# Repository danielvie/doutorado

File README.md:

# Doutorado

Repository for thesis writing, simulations, embedded experiments, presentations, publications, and supporting research material.

## Quick links

- Current thesis PDF: [`tese.pdf`](tese.pdf)
- Repository map: [`docs/REPO_MAP.md`](docs/REPO_MAP.md)
- Domain glossary: [`CONTEXT.md`](CONTEXT.md)
- Archived old root README notes: [`docs/README_NOTES_ARCHIVE.md`](docs/README_NOTES_ARCHIVE.md)
- Current working TODO/history: [`TODO`](TODO)

## Where to go

| Need | Go to |
| --- | --- |
| Thesis and paper LaTeX sources | [`LATEX/`](LATEX/) |
| Plans, TODOs, and qualification material | [`research-material/planning/`](research-material/planning/) |
| Reviewer comments | [`research-material/review-feedback/`](research-material/review-feedback/) |
| Authored analysis and meeting notes | [`research-material/working-notes/`](research-material/working-notes/) |
| Shared diagrams and writing assets | [`assets/`](assets/) |
| Current MATLAB simulations/control code | [`simulations/matlab-sim/`](simulations/matlab-sim/) |
| Older MATLAB simulations | [`simulations/legacy/`](simulations/legacy/) |
| Projection/feasibility-region MATLAB work | [`simulations/projection/`](simulations/projection/) |
| ESP32 firmware, hardware docs, and web UI | [`embedded/`](embedded/) |
| External papers, books, theses, and course material | [`research-material/literature/`](research-material/literature/) |
| Presentations and slides | [`presentations/`](presentations/) |
| External/vendor material | [`z_dependencies/`](z_dependencies/), [`z_kawa/`](z_kawa/), [`z_mpt_install/`](z_mpt_install/), and [`z_qpoases/`](z_qpoases/) |

## Common commands

This repository uses [`Taskfile.yml`](Taskfile.yml):

```sh
task --list
```

Important tasks:

- `task run` opens generated overview documentation.
- `task test` validates generated overview documentation.
- `task clean` removes generated overview documentation.
- `task update-tese` copies `LATEX/thesis/build/tese.pdf` to the repository root.

## Navigation conventions

- Start from this README, then use [`docs/REPO_MAP.md`](docs/REPO_MAP.md) for locations and [`CONTEXT.md`](CONTEXT.md) for terminology.
- Prefer area-specific READMEs/docs when they exist.
- Treat `z_dependencies/`, `z_kawa/`, `z_mpt_install/`, `z_qpoases/`, and `simulations/backup/` as backup, vendored, or auxiliary material unless a task explicitly points there.
- Prefer `simulations/matlab-sim/` over `simulations/legacy/` for current simulation work.
- Prefer `embedded/esp32_idf/` for current ESP32 firmware work.
- Avoid adding new loose files at the repository root; put new material in the closest project area.
- Keep document navigation folders at most three levels deep. Self-contained source/build trees are exempt when flattening would break them.

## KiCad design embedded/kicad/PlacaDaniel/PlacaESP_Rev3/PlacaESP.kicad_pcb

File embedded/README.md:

# Projeto embarcado

Workspace do projeto de doutorado para controle em tempo real com ESP32.

## Estrutura

- [`esp32_idf/`](esp32_idf/) — firmware ESP-IDF, protocolo BLE, interface web e documentação técnica do controlador de sinais.
- [`kicad/`](kicad/) — fontes das placas, bibliotecas de footprints/símbolos e arquivos de fabricação.
- [`docs-hardware/`](docs-hardware/) — pinagens, diagramas de conexão e datasheets de referência.
- [`tests_espressif/`](tests_espressif/) — experimentos independentes com ESP32/PlatformIO.

## Firmware

Consulte [`esp32_idf/README.md`](esp32_idf/README.md) para a arquitetura e os requisitos do firmware. Para listar os comandos disponíveis:

```sh
cd esp32_idf
task --list
```

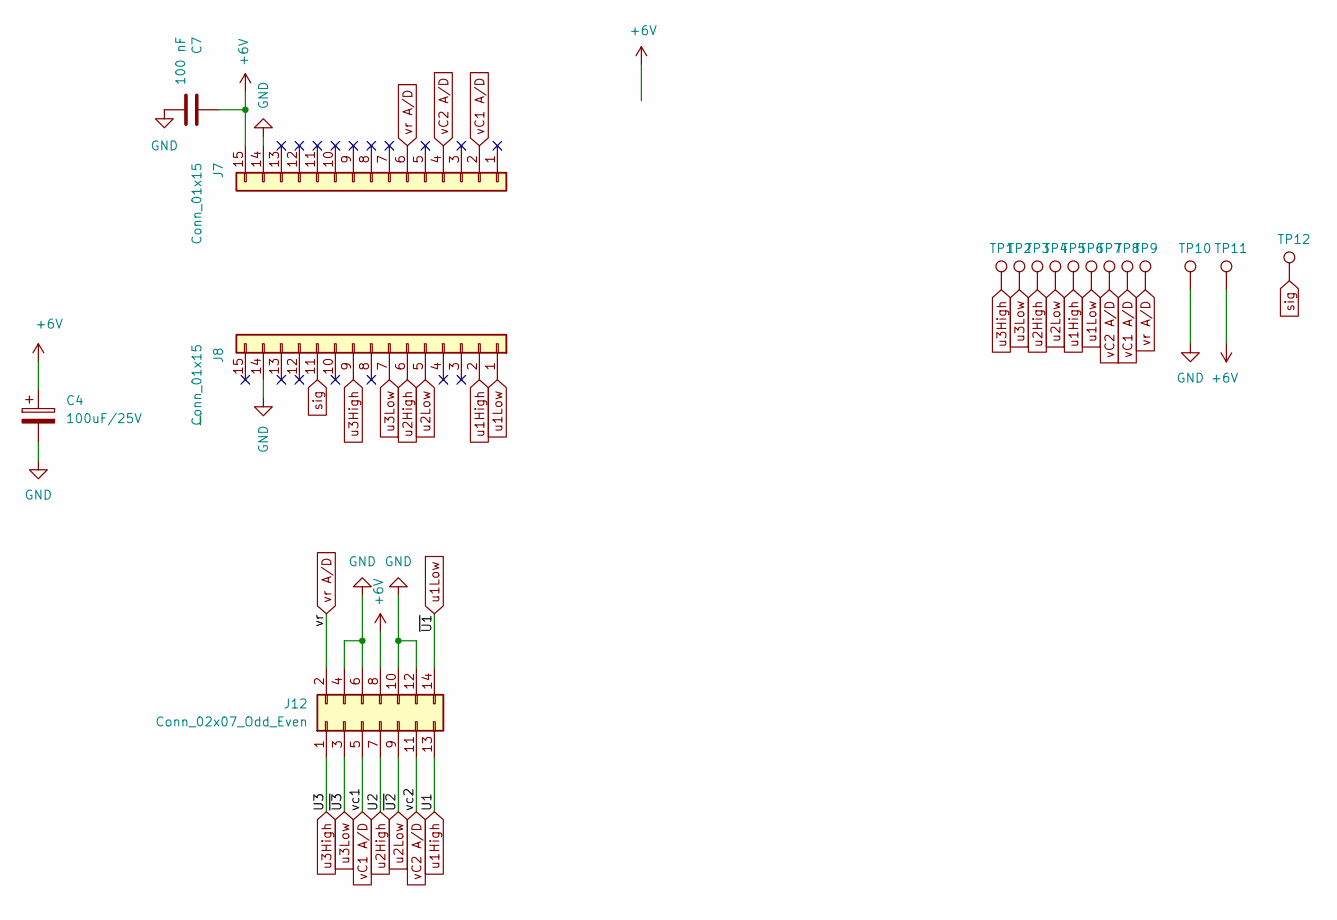
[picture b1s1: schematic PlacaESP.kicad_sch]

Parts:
C4: 100uF/25V; CP_Radial_D6.3mm_P2.50mm
C7: 100 nF; C_Disc_D6.0mm_W2.5mm_P5.00mm
J7, J8: Conn_01x15; PinSocket_1x15_P2.54mm_Vertical
J12: Conn_02x07_Odd_Even; IDC-Header_2x07_P2.54mm_Vertical
TP1, TP2, TP3, TP4, TP5, TP6, TP7, TP8, TP9, TP10, TP11, TP12: TestPoint_Bridge_Pitch2.54mm_Drill0.7mm

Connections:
+6V: C4.1, C7.1, J7.15, J12.8, TP11.1
GND: C4.2, C7.2, J7.14, J8.14, J12.4, J12.6, J12.10, J12.12, TP10.1
sig: J8.11, TP12.1
u1High: J8.2, J12.13, TP5.1
u1Low: J8.1, J12.14, TP6.1
u2High: J8.6, J12.7, TP3.1
u2Low: J8.5, J12.9, TP4.1
u3High: J8.9, J12.1, TP1.1
u3Low: J8.7, J12.3, TP2.1
vC1 A/D: J7.2, J12.5, TP8.1
vC2 A/D: J7.4, J12.11, TP7.1
vr A/D: J7.6, J12.2, TP9.1

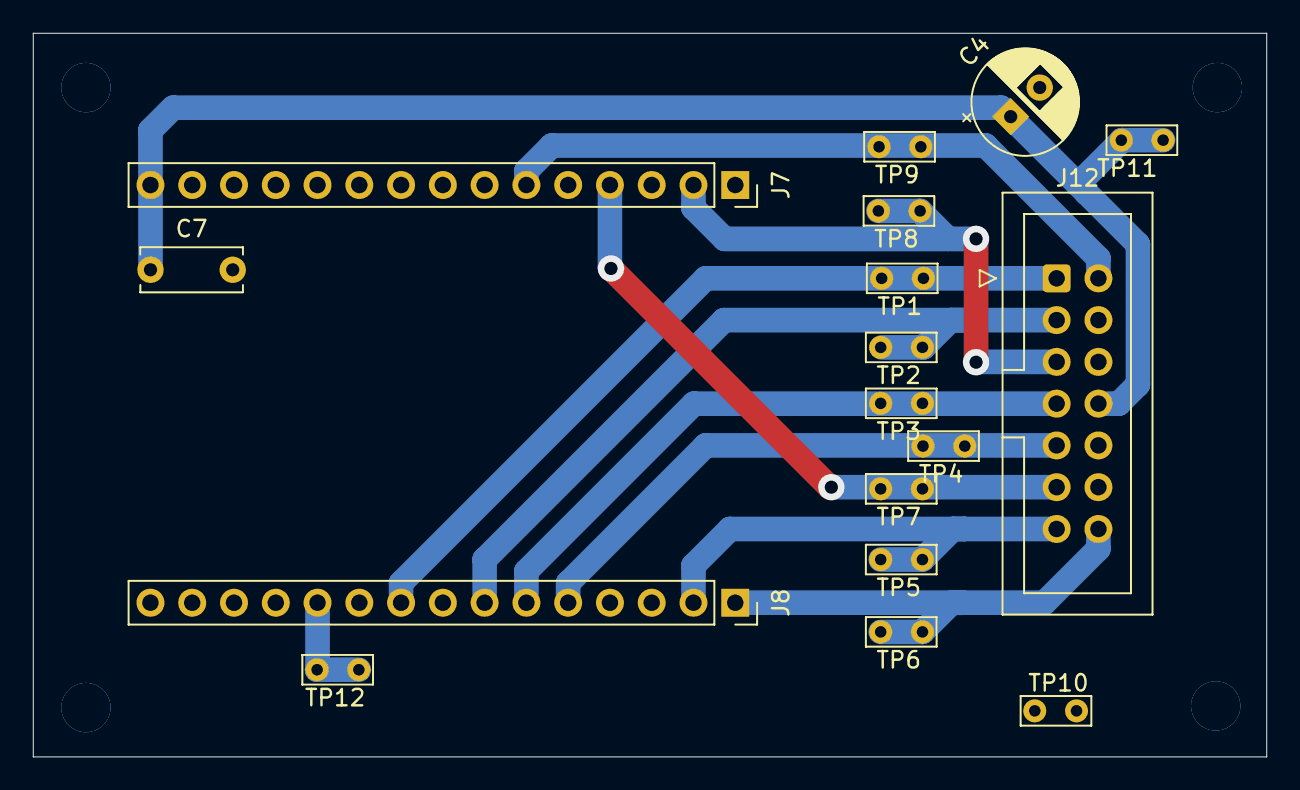
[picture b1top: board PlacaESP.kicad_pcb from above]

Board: 2 copper layers, 75.0 x 44.0 mm, 17 parts (0 on the bottom side), 12 nets.

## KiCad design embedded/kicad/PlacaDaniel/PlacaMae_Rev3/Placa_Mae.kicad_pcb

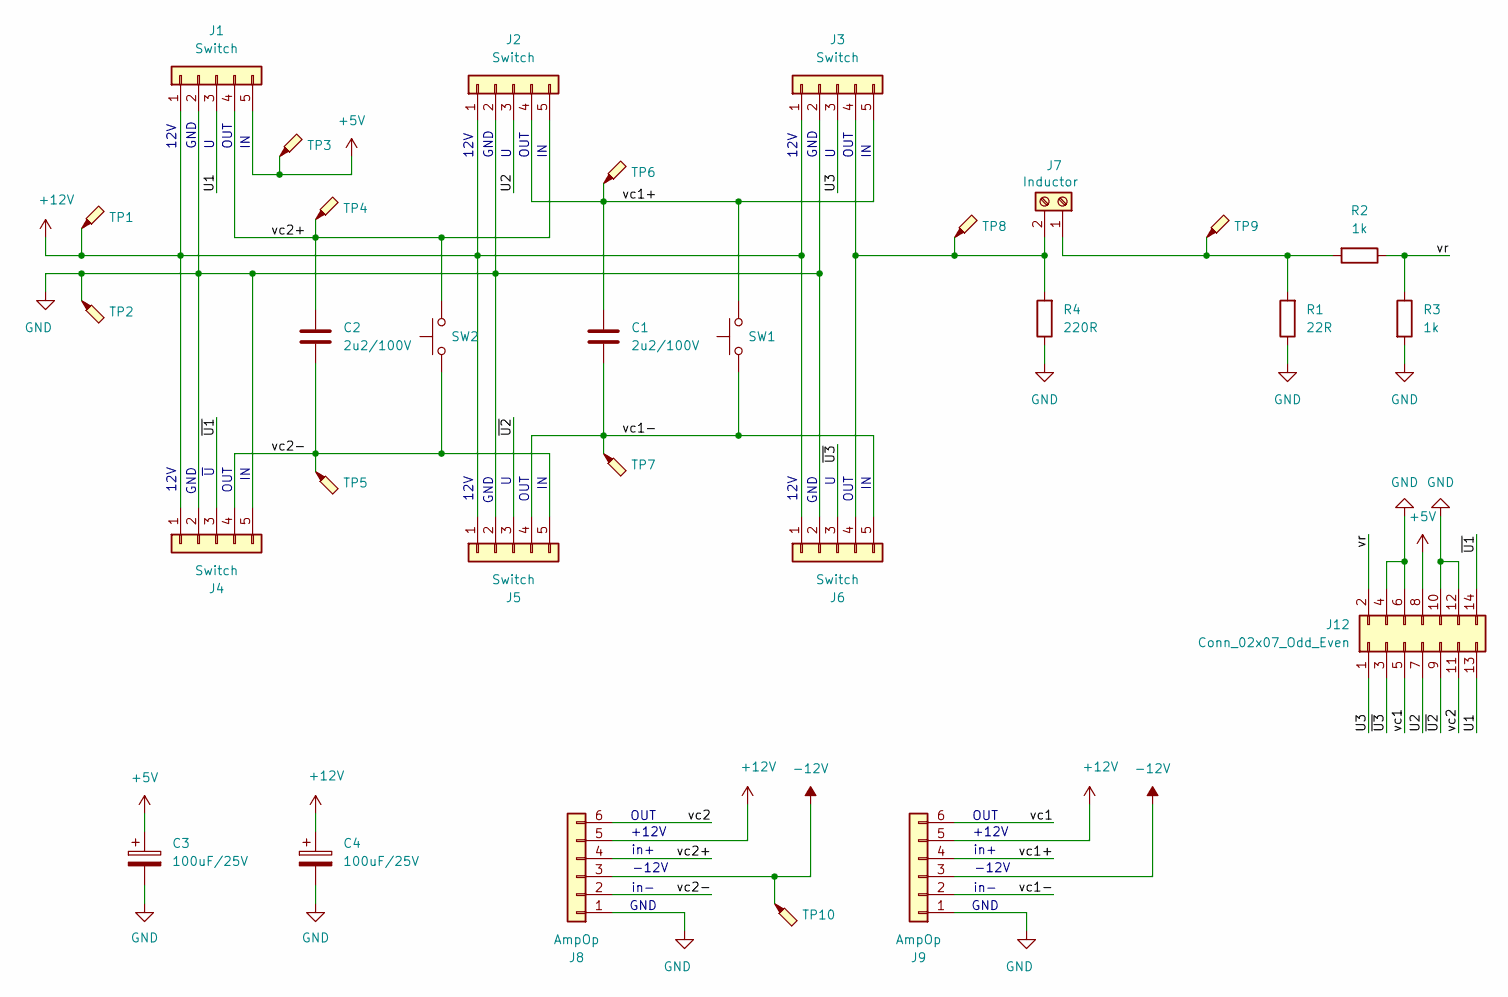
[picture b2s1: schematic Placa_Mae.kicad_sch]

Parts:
C1, C2: 2u2/100V; C_Rect_L29.0mm_W9.1mm_P27.50mm_MKT
C3, C4: 100uF/25V; CP_Radial_D6.3mm_P2.50mm
J1, J2, J3, J4, J5, J6: Switch; TerminalBlock_Xinya_XY308-2.54-5P_1x05_P2.54mm_Horizontal
J7: Inductor; TerminalBlock_Phoenix_MKDS-1,5-2_1x02_P5.00mm_Horizontal
J8, J9: AmpOp; TerminalBlock_Xinya_XY308-2.54-6P_1x06_P2.54mm_Horizontal
J12: Conn_02x07_Odd_Even; IDC-Header_2x07_P2.54mm_Vertical
R1: 22R; R_Axial_DIN0516_L15.5mm_D5.0mm_P25.40mm_Horizontal
R2, R3: 1k; R_1206_3216Metric_Pad1.30x1.75mm_HandSolder
R4: 220R; R_Axial_DIN0516_L15.5mm_D5.0mm_P25.40mm_Horizontal
SW1, SW2: SW_Push; SW_PUSH_6mm_H7.3mm
TP1, TP2, TP3, TP4, TP5, TP6, TP7, TP8, TP9, TP10: TestPoint_Probe; TestPoint_Bridge_Pitch5.08mm_Drill0.7mm

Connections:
+5V: C3.1, J1.5, J12.8, TP3.1
+12V: C4.1, J1.1, J2.1, J3.1, J4.1, J5.1, J6.1, J8.5, J9.5, TP1.1
-12V: J8.3, J9.3, TP10.1
/U1: J1.3, J12.13
/U2: J2.3, J12.7
/U3: J3.3, J12.1
/vc1: J9.6, J12.5
/vc1+: C1.1, J2.4, J3.5, J9.4, SW1.2, TP6.1
/vc1-: C1.2, J5.4, J6.5, J9.2, SW1.1, TP7.1
/vc2: J8.6, J12.11
/vc2+: C2.1, J1.4, J2.5, J8.4, SW2.2, TP4.1
/vc2-: C2.2, J4.4, J5.5, J8.2, SW2.1, TP5.1
/vr: J12.2, R2.1, R3.1
/~U1: J4.3, J12.14
/~U2: J5.3, J12.9
/~U3: J6.3, J12.3
GND: C3.2, C4.2, J1.2, J2.2, J3.2, J4.2, J4.5, J5.2, J6.2, J8.1, J9.1, J12.4, J12.6, J12.10, J12.12, R1.1, R3.2, R4.1, TP2.1
unnamed: J3.4, J6.4, J7.2, R4.2, TP8.1
unnamed: J7.1, R1.2, R2.2, TP9.1

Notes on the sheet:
OUT
GND
12V
+12V
in-
in+
~{U}
-12V

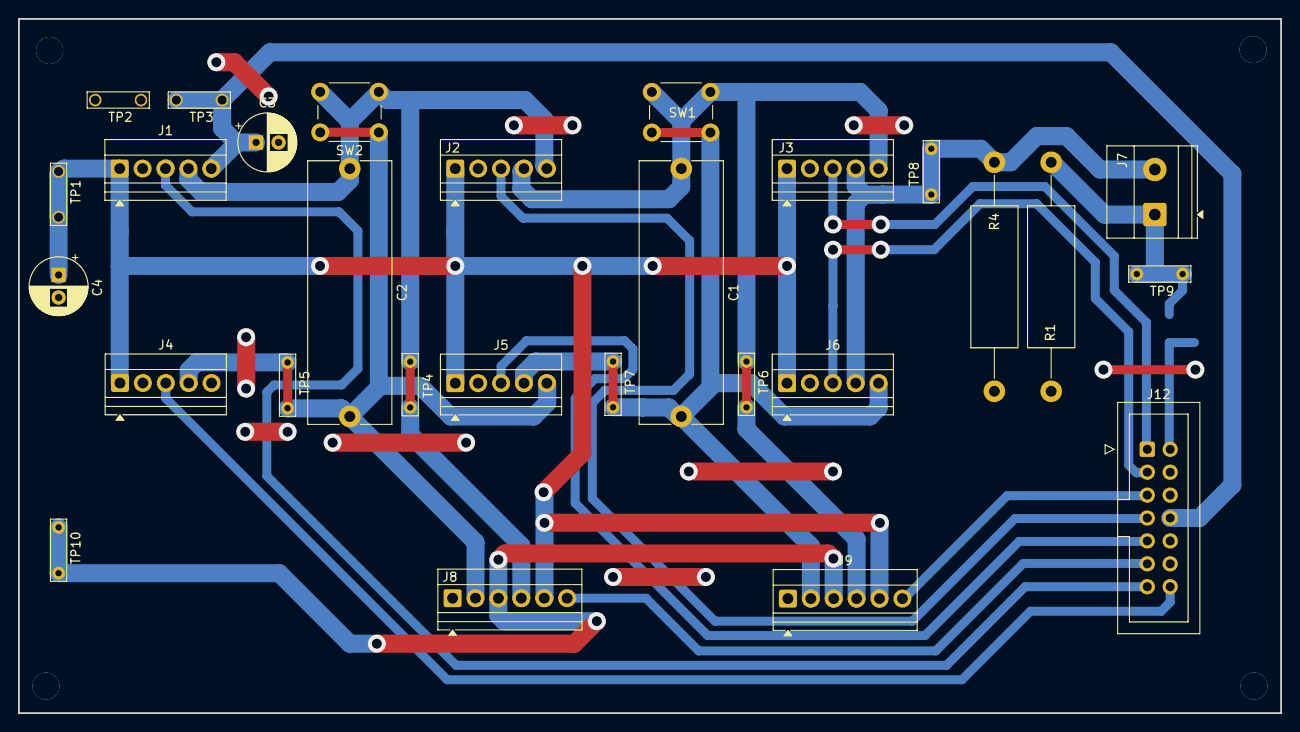
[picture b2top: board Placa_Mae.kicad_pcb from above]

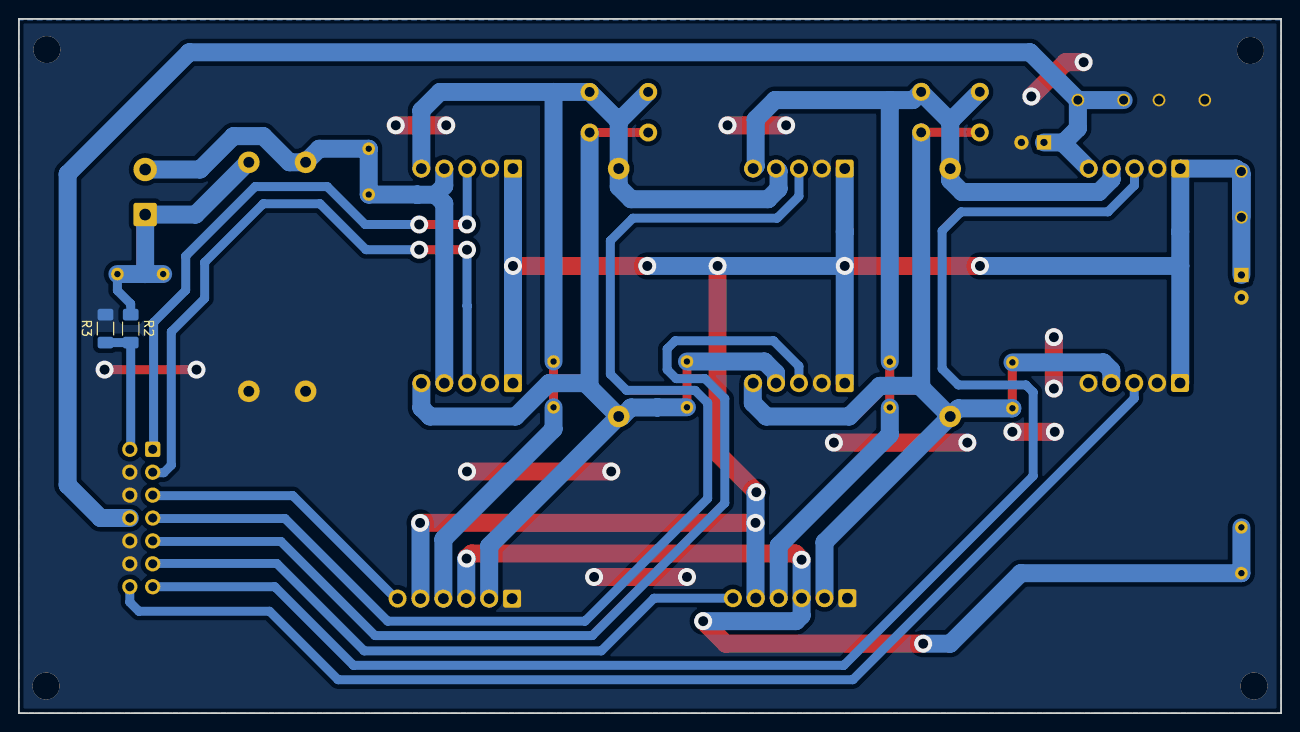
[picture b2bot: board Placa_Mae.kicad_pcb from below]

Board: 2 copper layers, 140.0 x 77.0 mm, 30 parts (2 on the bottom side), 19 nets.

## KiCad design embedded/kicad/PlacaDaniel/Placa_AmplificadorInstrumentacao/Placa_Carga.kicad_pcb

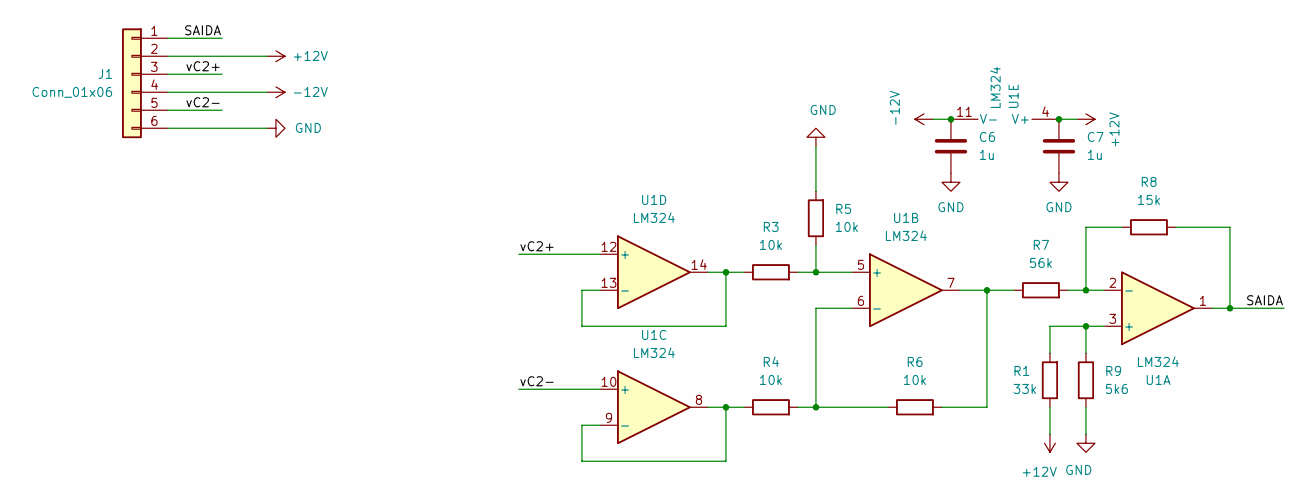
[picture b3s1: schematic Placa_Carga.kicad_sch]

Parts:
C6, C7: 1u; C_1206_3216Metric_Pad1.33x1.80mm_HandSolder
J1: Conn_01x06; PinHeader_1x06_P2.54mm_Vertical
R1: 33k; R_1206_3216Metric_Pad1.30x1.75mm_HandSolder
R3, R4, R5, R6: 10k; R_1206_3216Metric_Pad1.30x1.75mm_HandSolder
R7: 56k; R_1206_3216Metric_Pad1.30x1.75mm_HandSolder
R8: 15k; R_1206_3216Metric_Pad1.30x1.75mm_HandSolder
R9: 5k6; R_1206_3216Metric_Pad1.30x1.75mm_HandSolder
U1: LM324; DIP-14_W7.62mm

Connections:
+12V: C7.1, J1.2, R1.1, U1.4 (V+)
-12V: C6.1, J1.4, U1.11 (V-)
/SAIDA: J1.1, R8.2, U1.1
/vC2+: J1.3, U1.12 (+)
/vC2-: J1.5, U1.10 (+)
GND: C6.2, C7.2, J1.6, R5.2, R9.2
unnamed: R6.2, R7.1, U1.7
unnamed: R1.2, R9.1, U1.3 (+)
unnamed: R7.2, R8.1, U1.2 (-)
unnamed: R3.2, R5.1, U1.5 (+)
unnamed: R4.2, R6.1, U1.6 (-)
unnamed: R4.1, U1.8, U1.9 (-)
unnamed: R3.1, U1.13 (-), U1.14

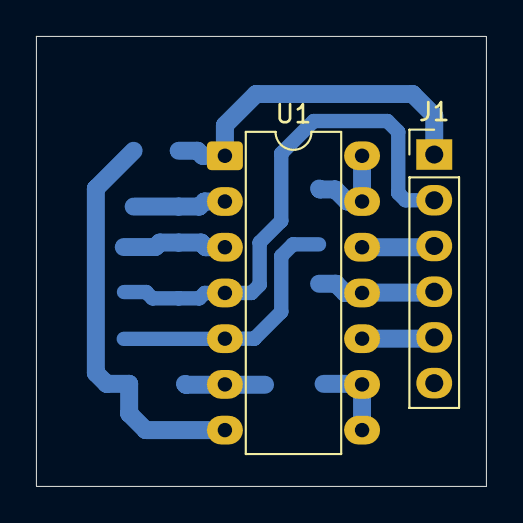
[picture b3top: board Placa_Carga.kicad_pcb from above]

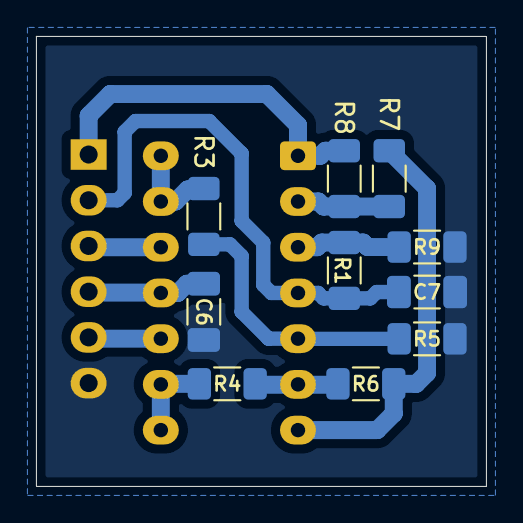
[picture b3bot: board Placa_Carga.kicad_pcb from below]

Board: 2 copper layers, 25.0 x 25.0 mm, 12 parts (10 on the bottom side), 13 nets.

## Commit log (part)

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2025-08-27 iter
2025-08-27 adding articles in circuit reference
2025-08-27 pre-reuniao
2025-08-28 setting alpha with lookup data
2025-08-31 update artigo
2025-09-01 improve layout web interface
2025-09-01 create custom printer function to control state
2025-09-01 restore bracked on same line style
2025-09-02 add figure with measurement points
2025-09-03 adicionar texto com analise dos experimentos
2025-09-06 update web and circuit labels ink
2025-09-09 update esp32 labels
2025-09-09 improve proportions on esp32 diagram
2025-09-10 add macos as a target for the web pipeline
2025-09-12 adding hw measure points to web
2025-09-14 make sure timer is initialized before pause
2025-09-14 adding MIT license to software
2025-09-15 update ble logic to reconnect without dialog
2025-09-15 implement freeRTOS queue for sending BLE message
2025-09-22 update interfact modes with u1, 2, 3
2025-09-24 sync latex with overleaf
2025-09-24 pre reuniao
2025-11-10 remove heart_rate_mock
2025-11-10 add DELAY:{}
2025-11-11 convert to cpp
2025-11-21 add `ble_send_message`
2025-11-21 generating signal with a IDLE burst for the WD
2025-11-21 disabled WDT on CORE1 and removed IDLE burst
2025-11-22 added blink onconnect/disconnect
2025-11-22 organize folders
2025-11-22 sending analog read every 500ms
2025-11-23 rename led -> helper_led, silent mode for BLE msg
2025-11-23 improve note logic
2025-11-24 creating ble_router.* functions
2025-11-24 implement STATUS and MATRIX messages
2025-11-26 remove led_strip dependency
2025-11-26 improve note_*
2025-11-27 test
2025-11-27 fix webserver issue
2025-11-28 remove aliasing on chart
2025-12-01 adjust code naming
2025-12-04 changing condition_dtk to linear law
2025-12-19 updating pinout reference images
2025-12-20 adding custom cycle delay function
2025-12-31 update svg esp32 pinout
2026-01-21 rewrite session 6.1 and 6.2
2026-01-21 rewrite web application
2026-01-21 improving simulation architecture iter
2026-02-09 update layout with antigravity
2026-02-16 add documentation
2026-02-16 refactor @Simulation
2026-02-17 add :: try to connect when send BLE
2026-02-17 add :: test controler cpp
2026-02-20 implementando recomentadoes professor rubens
2026-03-19 put classic simulation back
2026-03-20 fix projection patino1
2026-03-20 fix projection patino2
2026-03-20 iter simu2
2026-03-20 improve projection patino2
2026-03-20 trying to match simulation projection with isolated projection
2026-03-20 implementing projection on patino1
2026-03-20 trying to fix project duplo integrador
2026-03-20 fixed patino2
2026-03-20 iter
    trying to fix patino2
2026-03-24 feat: Add simulation scripts for Patino 1 and Patino 2 models, comparing MPC with proportional and uncontrolled strategies.
2026-03-24 feat: Introduce Python implementations for Patiño1 and Integrador Duplo feasibility region computation, including documentation and generated plots.
2026-03-27 iter lab
2026-03-28 pos reuniao
2026-03-30 add taskfile
2026-03-30 adjust zed setting to work with project clangd linting
2026-04-17 removing PID again
2026-04-17 removeing dead comments
2026-04-17 implementing optimization
2026-04-17 reverting optimization 1
2026-04-17 fix build system for macos
2026-04-17 adjust clangd for macos
2026-04-18 performance improvement
2026-04-18 Refactor and performance improvement
    Replace the 4k-line if-else chain in helper_datasetter.cpp with a static
    std::map containing lambdas for O(log n) lookup. Add missing
    MASK_U1_HIGH, MASK_U2_LOW, and MASK_U3_LOW/HIGH constants to signal_controller.h.
    Update React component variable names to snake_case per TigerBeetle naming
    conventions.
2026-04-19 Restructure docs and add guides, API reference, theory
    Add GETTING_STARTED, COOKBOOK, API_REFERENCE, and THEORY docs.
    Reorganize existing documentation into legacy/ and agent/ folders.
    Rewrite README. Remove temporary bla.m script.
2026-04-19 Reorganize simu2 into +z_run package structure
    Organize scripts, tests, demos and utilities into categorized
    subpackages under +z_run. Add task runner interface in t.m for
    common workflows. Move design files and figures to dedicated
    folders. Remove obsolete backup scripts.
2026-04-21 adding pragmatic DnD
2026-04-21 feat: implement drag-and-drop dashboard UI with persistent layout and add project documentation
2026-04-22 Add web:all task to run webserver and agentation
2026-04-23 Rename dashboard panels and restyle header
    RealtimeChart, SignalControl, and ManualControl
    are now SignalAnalysis, SignalGenerator, and SystemLogs. Remove
    decorative header icons from all panels. Redesign top header
    with compact layout and connection-state-aware button styles.
    Add warning button variant and refine danger button hover
    state.
2026-04-24 update support images
2026-04-24 update web taskfile
2026-04-25 Switch to table-driven lookup generator
2026-04-25 feat: initialize project structure including simulation tools, embedded systems firmware, and documentation assets
2026-04-25 feat: add project research files, embedded controller implementations, LaTeX documentation, and simulation frameworks
2026-04-25 Add mock data toggle for offline testing
2026-04-25 add react compiler
2026-04-25 Add analysis report and optimize Zustand selectors
    Add comprehensive architecture, security, and performance analysis
    report.
    Optimize Zustand store subscriptions across all dashboard components to
    use individual selectors, preventing unnecessary re-renders when
    unrelated store fields change. Fix Taskfile web commands and add step
    attribute to SignalAnalysis maxPoints input.
2026-04-25 Add alpha field to dataset and include in BLE status
    Move monitorPeriodMs to global bleStore for mock frequency control
2026-04-25 implementing protobuf messaging
2026-04-25 Implement Protobuf hybrid protocol and Status panel improvements
    * Add binary discriminator (0x01) for Protobuf packets over BLE.
    * Implement SystemStatus and LogMessage Protobuf schemas.
    * Update Status panel and System Logs with copy-to-clipboard functionality.
    * Add visual feedback (Copied! badge) for clipboard actions.
    * Replace ASCII status string with structured binary reporting on ESP32.
2026-04-26 Fix Protobuf status mapping and add UI features
    * Handle Proto3 default values (numeric 0) in BleManager
    * Implement inline manual editing for Duty Cycle (Alpha)
    * Integrate Agentation client for visual feedback
    * Refactor signal loop with maintenance windows for stability
    * Synchronize atomic state across control and BLE cores
2026-04-26 Implement state-driven LED manager with dynamic delays
    - Replace manual blink tasks with a centralized queue-driven manager
    - Formalize LED modes in system state and Protobuf telemetry
    - Synchronize cross-core state using atomic variables
    - Support asymmetric blink patterns via dynamic delay updates
    - Update web dashboard to display current LED indicator mode
2026-04-27 Add Hardware Visualization modal to dashboard
    - Implement paginated fullscreen modal for hardware reference
    - Add ESP32 pinout, schematic, and measurement point views
    - Add "Hardware" access button to dashboard header
    - Support sequential navigation between hardware diagrams
2026-04-27 Add Unix nanopb support and status refresh button
2026-04-27 Optimize signal generation and refactor ImageModal
    - Implement pre-computed SignalSteps to save Core 1 CPU cycles
    - Add 10ms latency safety check to prevent interrupt starvation
    - Refactor ImageModal to accept generic image data via props
    - Add hardware visualization button and modal to dashboard header
    - Document hardware safety masks and optimization logic
2026-04-28 Fix BLE throughput: conn interval and send size
    Send actual content length in note_ble_send instead of full buffer capacity (497 → idx). Negotiate 7.5 ms connection interval on client connect for ~6.5× throughput improvement.
2026-04-28 feat: implement Protobuf definitions and serialization for system telemetry and status messaging
2026-04-28 Optimize BLE communication and status reporting
    Offload BLE command processing to a background task and implement
    TX congestion tracking. Add a "Congested" warning to the web dashboard
    and include chip info logging at startup. Update analysis docs.
2026-04-28 Implement ADC latency monitoring and auto-status polling
    - Add high-precision latency tracking with 128-sample circular buffer
    - Include min, max, and avg ADC latency in SystemStatus telemetry
    - Implement automatic status polling toggle in web dashboard
    - Optimize BLE communication by avoiding redundant UI components
2026-04-30 Add structured UI command router with protobuf schema
    - Introduce UiCommand/UiCommandResult protobuf messages for namespaced
    commands with JSON payloads (e.g., "signal.start")
    - Add ui_command_router module with handler registry and input validation
    (reject cycles:0, period_ms:0, invalid JSON)
    - Migrate web client from text commands to sendCommand() with typed payloads
    - Add CODE_DESIGN_ANALYSIS_REPORT.md documenting architecture risks
2026-04-30 Migrate BLE to binary protocol and remove legacy UI
    Increase UiCommandResult JSON buffer size from 384 to 512 bytes.
    Add ble_send_* functions to replace ble_router_* variants.
    Add analog read commands and BLE transmission helpers.
    Remove legacy web UI components and old bluetooth.ts implementation.
    Enforce binary-only BLE communication by removing string send methods.
    Clean up signal parsing and remove dead blink task code.
2026-04-30 Refactor signal loop, rename BLE modules, add UI search
    Split signal_loop_task into focused static helpers, keeping
    interrupt-disabled
    GPIO playback isolated for jitter-free timing. Rename UI command router
    and
    OTA controller files to ble_* prefix. Add signal.set_dead_time_all
    command
2026-04-30 update to run on mac
2026-05-01 test on mac
2026-05-01 improve connection recover
2026-05-01 improve OTA flasher
2026-05-01 update OTA flash
2026-05-05 Refactor MPC control setup
    Move runtime control state (.on, .x_target) from config.mpc to
    config.control. Pass solver_options to the QP solver and add
    validation guards to fail early when control is used without
    prior setup. Update docs and call sites.
2026-05-07 Add cycle-based signal timing and web UI features
    - Switch Core 1 signal loop from microsecond to cycle-accurate delays
    using precomputed duration_cycles to eliminate jitter
    - Add debug.signal_timing command returning JSON timing snapshot
    including per-loop min/max/avg overhead
    - Replace alpha buttons with 0.1-0.9 preset grid and add copy buttons
    for vectors and total duration in web signal generator
2026-05-10 add kicad design
2026-05-11 Refactor signal loop to absolute edge deadlines
    Replace per-segment delays with absolute cycle deadlines to eliminate
    timing drift. Batch short patterns to reduce loop overhead. Add
    overrun, fault, clamp and maintenance-skip counters. Shorten timing
    JSON keys for BLE MTU; update web parser to support both old and new
    keys.
2026-05-11 Collapse dead time to symmetric single value
2026-05-13 document dead-time and signal logic in HTML
2026-05-14 add code highlight to code blocks
2026-05-14 add documento analysis of analog measurement
2026-05-14 implementing optimization analog read. part 1
2026-05-14 implementing optimization analog read. part 2
2026-05-14 implementing optimization analog read. implementing plan 2
2026-05-14 implementing optimization analog read. testing
2026-05-14 feat: add HelpPanel component for browsing and testing BLE commands
2026-05-14 remove embedded/esp32
2026-05-14 remove wt analysis
2026-05-15 update documentation
2026-05-21 creating signal generator
2026-06-01 organize latex project
2026-06-01 random updates
2026-06-01 improve cap 3 and feasibility session
2026-06-01 rewriting chapter 3
2026-06-11 Normalize signal timing units to 0.1 µs
2026-06-11 update matlab simulation to compute 0.1 us precision
